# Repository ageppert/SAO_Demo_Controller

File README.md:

# SAO DEMO CONTROLLER

A Microcontroller for your smarter-than-average SAO!

The SAO Demo Controller makes it convenient to bring life to your advanced I2C-based SAO! Use this to test and demonstrate your new design even when your host badge isn't ready to control the SAO. Maybe this is better referred to as a micro badge for developing SAOs.

CAUTION: Do not plug this into your host badge and USB-C at the same time!!!

Follow this project at: https://hackaday.io/project/198034-sao-demo-controller 

Hardware Version 3.X
This one is protected for multiple power input options simultaneously with far more advanced power options, protection, and routing. This one is a perfect companion for an Etch sAo Sketch, Mac SAO, or any other SAO! See schematic for details and instructions.

Hardware Version 2.0 

Hardware Version 1.0

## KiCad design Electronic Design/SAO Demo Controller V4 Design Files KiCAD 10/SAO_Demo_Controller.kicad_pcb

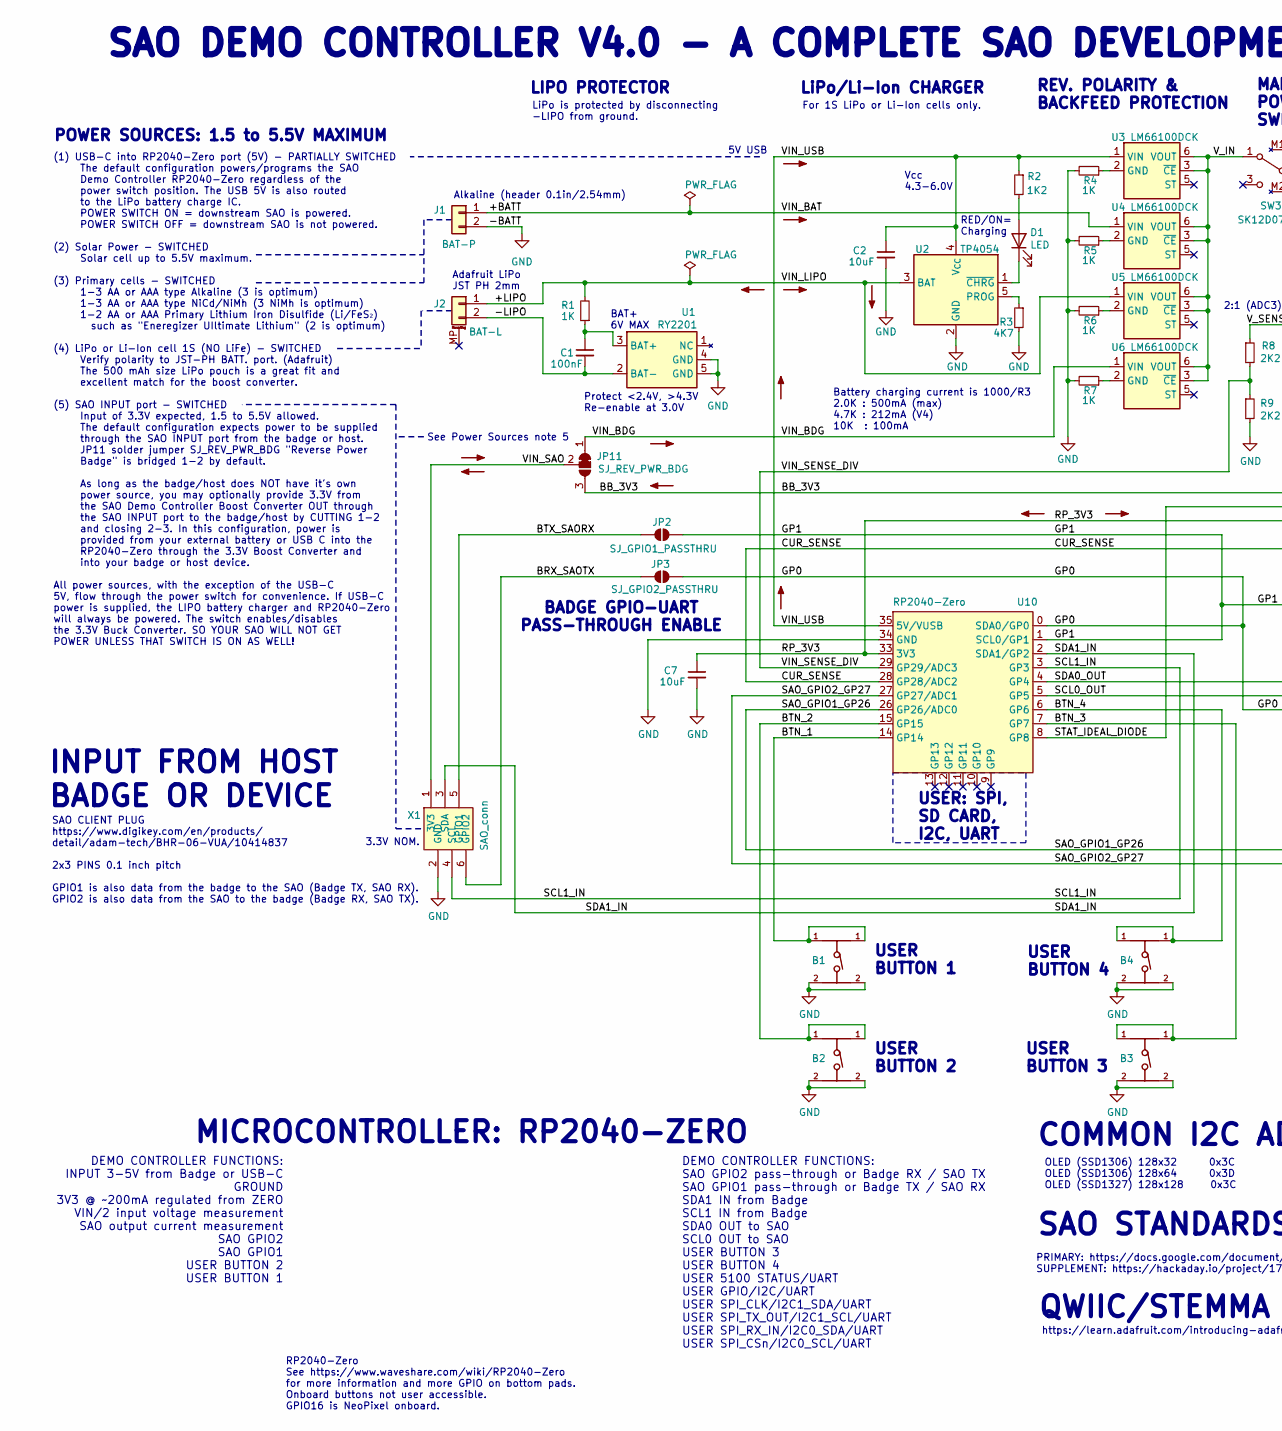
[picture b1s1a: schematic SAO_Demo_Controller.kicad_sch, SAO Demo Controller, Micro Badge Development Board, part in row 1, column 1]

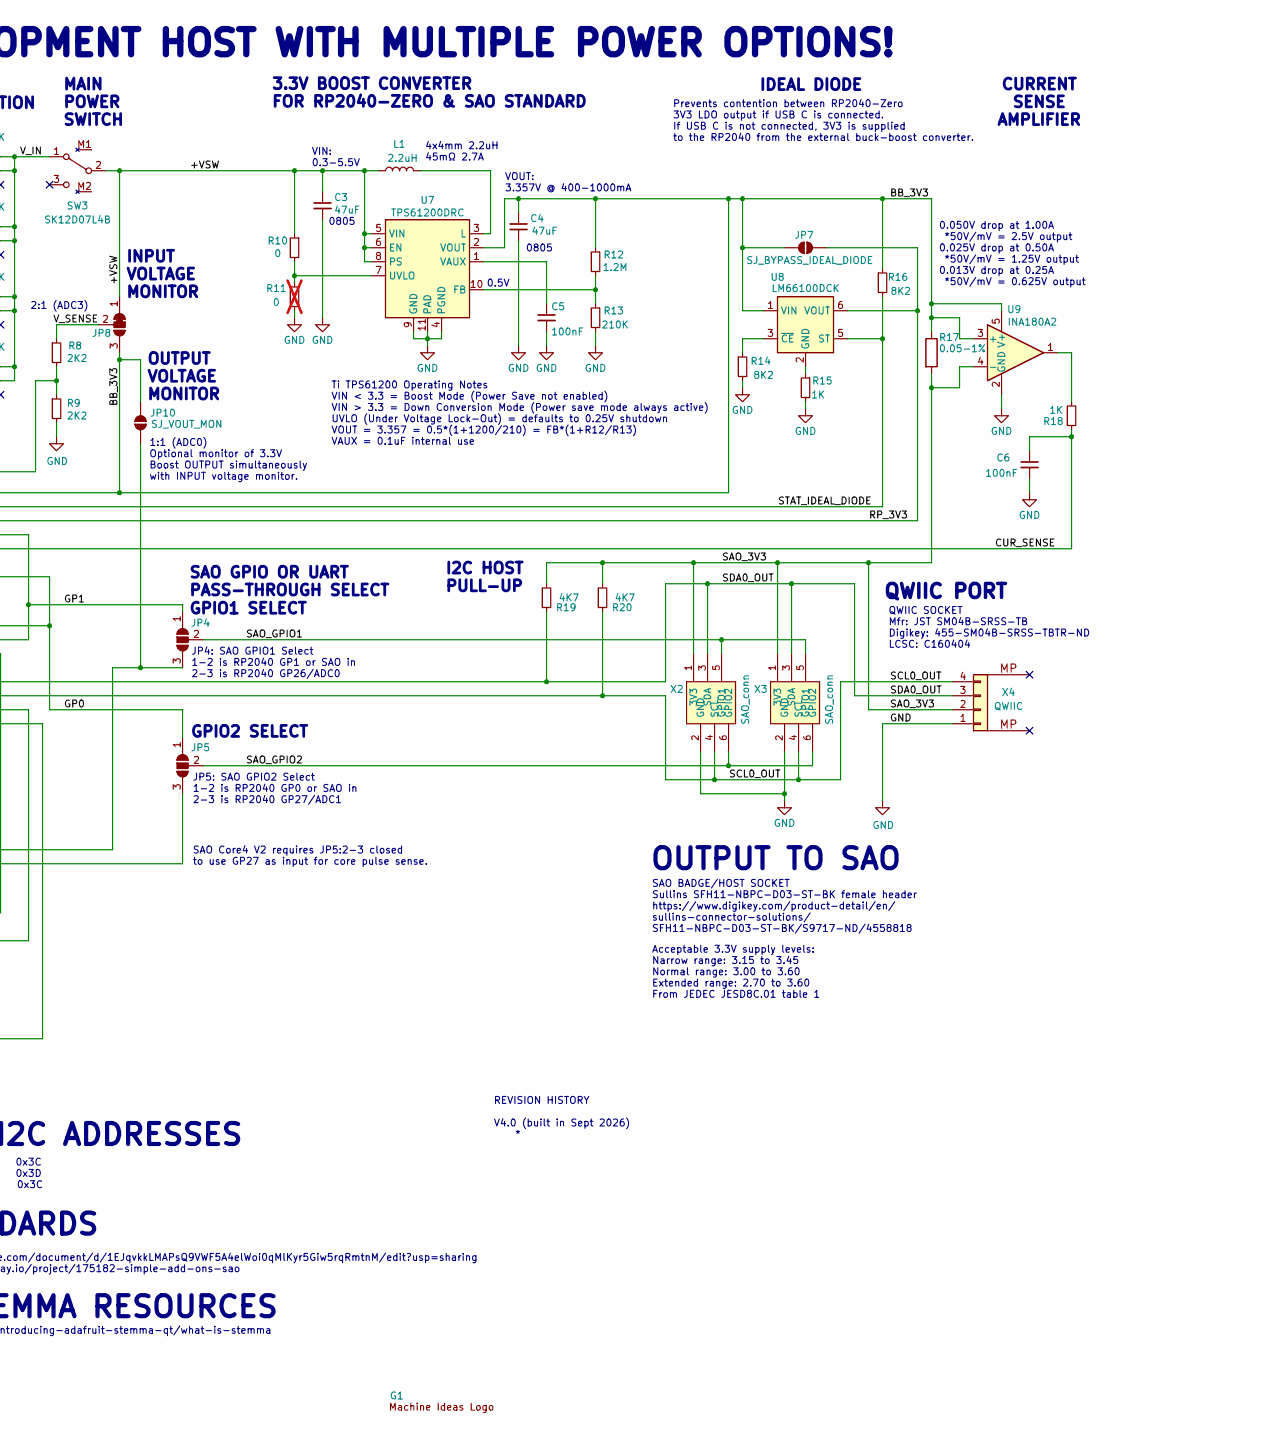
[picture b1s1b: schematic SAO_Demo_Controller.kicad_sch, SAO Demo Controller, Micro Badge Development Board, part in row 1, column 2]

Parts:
B1, B2, B3, B4: EVQP7J01P; SMD4_SW_EVQP7J_PAN; LCSC C2828254
C1, C5, C6: 100nF; C_0603_1608Metric; LCSC C14663
C2, C7: 10uF; C_0603_1608Metric; LCSC C19702
C3, C4: 47uF; C_0805_2012Metric; PART-NUMBER 10V 47uF X5R ±20% 0805; LCSC C16780
D1: LED; LED_0603_1608Metric; LCSC C2286
G1: Machine_Ideas_logo
J1: BAT-P; PinSocket_1x02_P2.54mm_Vertical
J2: BAT-L; JST_PH_S2B-PH-SM4-TB_1x02-1MP_P2.00mm_Horizontal; LCSC C295747
JP2: SJ_GPIO1_PASSTHRU; SolderJumper-2_P1.3mm_Open_RoundedPad1.0x1.5mm
JP3: SJ_GPIO2_PASSTHRU; SolderJumper-2_P1.3mm_Open_RoundedPad1.0x1.5mm
JP4, JP5: SolderJumper_3_Open; SolderJumper-3_P1.3mm_Open_RoundedPad1.0x1.5mm_NumberLabels
JP7: SJ_BYPASS_IDEAL_DIODE; SolderJumper-2_P1.3mm_Open_RoundedPad1.0x1.5mm
JP8: SolderJumper_3_Open; SolderJumper-3_P1.3mm_Bridged12_RoundedPad1.0x1.5mm
JP10: SJ_VOUT_MON; SolderJumper-2_P1.3mm_Open_RoundedPad1.0x1.5mm
JP11: SJ_REV_PWR_BDG; SolderJumper-3_P1.3mm_Bridged12_RoundedPad1.0x1.5mm
L1: 2.2uH; L_Sunlord_SWPA4020S; PART-NUMBER Sunltech Tech SLW4018S2R2MST; LCSC C206341
R1, R4, R5, R6, R7, R15, R18: 1K; R_0603_1608Metric; LCSC C21190
R2: 1K2; R_0603_1608Metric; LCSC C22765
R3, R19, R20: 4K7; R_0603_1608Metric; LCSC C23162
R8, R9: 2K2; R_0603_1608Metric; Manufacturer_Part_Number 0603WAF2201T5E; LCSC C4190
R10: 0; R_0603_1608Metric; LCSC C21189
R11: 0; R_0603_1608Metric; LCSC C21189; not fitted
R12: 1.2M; R_0603_1608Metric; LCSC C22766
R13: 210K; R_0603_1608Metric; LCSC C50670454
R14, R16: 8K2; R_0603_1608Metric; LCSC C25981
R17: 0.05-1%; R_0805_2012Metric; LCSC C5141277
SW3: SK12D07L4B; Switch_SK12D07VG4; LCSC C480340
U1: RY2201; SOT-23-5_HandSoldering; LCSC C370889
U2: TP4054; SOT-23-5; LCSC C32574
U3, U4, U5, U6, U8: LM66100DCK; SOT-363_SC-70-6; LCSC C2869734
U7: TPS61200DRC; Texas_S-PVSON-N10_ThermalVias; LCSC C140320
U9: INA180A2; SOT-23-5; LCSC C48533471
U10: RP2040-Zero; RP2040 Zero
X1: SAO_conn; Badgelife-SAOv169-BADGE-2x3-no-front-text; MPN SFH11-NBPC-D03-ST-BK
X2, X3: SAO_conn; Badgelife-SAOv169-BADGE-2x3-no-front-text-yes-front-outline; MPN SFH11-NBPC-D03-ST-BK
X4: QWIIC; JST_SH_SM04B-SRSS-TB_1x04-1MP_P1.00mm_Horizontal; MPN SM04B-SRSS-TB; LCSC C160404

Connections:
/+BATT: J1.1, U4.1 (VIN)
/+LIPO: J2.1, R1.2, U2.3 (BAT), U5.1 (VIN)
/+VSW: C3.1, JP8.1 (A), L1.2, R10.1, SW3.2 (B), U7.5 (VIN), U7.6 (EN), U7.8 (PS)
/-LIPO: C1.2, J2.2, U1.2 (BAT-)
/BB_3V3: C4.1, JP7.1 (A), JP8.3 (B), JP10.2 (B), JP11.3 (B), R12.1, R16.1, R17.1, U7.2 (VOUT), U8.1 (VIN), U9.3 (+), U9.5 (V+)
/BRX_SAOTX: JP3.1 (A), X1.6 (GPIO2)
/BTN_1: B1.1, U10.14 (GP14)
/BTN_2: B2.1, U10.15 (GP15)
/BTN_3: B3.1, U10.7 (GP7)
/BTN_4: B4.1, U10.6 (GP6)
/BTX_SAORX: JP2.1 (A), X1.5 (GPIO1)
/CUR_SENSE: C6.1, R18.1, U10.28 (GP28/ADC2)
/GP0: JP3.2 (B), JP5.1 (A), U10.0 (SDA0/GP0)
/GP1: JP2.2 (B), JP4.1 (A), U10.1 (SCL0/GP1)
/RP_3V3: C7.1, JP7.2 (B), U8.6 (VOUT), U10.33 (3V3)
/SAO_3V3: R17.2, R19.2, R20.2, U9.4 (-), X2.1 (3V3), X3.1 (3V3), X4.2
/SAO_GPIO1: JP4.2 (C), X2.5 (GPIO1), X3.5 (GPIO1)
/SAO_GPIO1_GP26: JP4.3 (B), JP10.1 (A), U10.26 (GP26/ADC0)
/SAO_GPIO2: JP5.2 (C), X2.6 (GPIO2), X3.6 (GPIO2)
/SAO_GPIO2_GP27: JP5.3 (B), U10.27 (GP27/ADC1)
/SCL0_OUT: R20.1, U10.5 (GP5), X2.4 (SCL), X3.4 (SCL), X4.4
/SCL1_IN: U10.3 (GP3), X1.4 (SCL)
/SDA0_OUT: R19.1, U10.4 (GP4), X2.3 (SDA), X3.3 (SDA), X4.3
/SDA1_IN: U10.2 (SDA1/GP2), X1.3 (SDA)
/STAT_IDEAL_DIODE: R16.2, U8.5 (ST), U10.8 (GP8)
/VIN_BDG: JP11.1 (A), U6.1 (VIN)
/VIN_SAO: JP11.2 (C), X1.1 (3V3)
/VIN_SENSE_DIV: R8.2, R9.1, U10.29 (GP29/ADC3)
/VIN_USB: C2.1, R2.1, U2.4 (V_{CC}), U3.1 (VIN), U10.35 (5V/VUSB)
/V_IN: SW3.1 (A), U3.3 (~CE), U3.6 (VOUT), U4.3 (~CE), U4.6 (VOUT), U5.3 (~CE), U5.6 (VOUT), U6.3 (~CE), U6.6 (VOUT)
/V_SENSE: JP8.2 (C), R8.1
GND: B1.2, B2.2, B3.2, B4.2, C2.2, C3.2, C4.2, C5.2, C6.2, C7.2, J1.2, R3.2, R4.2, R5.2, R6.2, R7.2, R9.2, R11.2, R13.2, R14.2, R15.2, U1.4 (GND), U1.5 (GND), U2.2 (GND), U7.4 (PGND), U7.9 (GND), U7.11 (PAD), U9.2 (GND), U10.34 (GND), X1.2 (GND), X2.2 (GND), X3.2 (GND), X4.1
unnamed: D1.2 (A), R2.2
unnamed: D1.1 (K), U2.1 (~CHRG)
unnamed: R18.2, U9.1
unnamed: C1.1, R1.1, U1.3 (BAT+)
unnamed: R3.1, U2.5 (PROG)
unnamed: R4.1, U3.2 (GND)
unnamed: R5.1, U4.2 (GND)
unnamed: R6.1, U5.2 (GND)
unnamed: R7.1, U6.2 (GND)
unnamed: R12.2, R13.1, U7.10 (FB)
unnamed: L1.1, U7.3 (L)
unnamed: R10.2, R11.1, U7.7 (UVLO)
unnamed: C5.1, U7.1 (VAUX)
unnamed: R15.1, U8.2 (GND)
unnamed: R14.1, U8.3 (~CE)

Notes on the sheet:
5V USB
REV. POLARITY & BACKFEED PROTECTION
SAO GPIO OR UART PASS-THROUGH SELECT
DEMO CONTROLLER FUNCTIONS: INPUT 3-5V from Badge or USB-C GROUND 3V3 @ ~200mA regulated from ZERO VIN/2 input voltage measurement SAO output current measurement SAO GPIO2 SAO GPIO1 USER BUTTON 2 USER BUTTON 1
Battery charging current is 1000/R3 2.0K : 500mA (max) 4.7K : 212mA (V4) 10K : 100mA
VOUT: 3.357V @ 400-1000mA
SAO BADGE/HOST SOCKET Sullins SFH11-NBPC-D03-ST-BK female header https://www.digikey.com/product-detail/en/ sullins-connector-solutions/ SFH11-NBPC-D03-ST-BK/S9717-ND/4558818
For 1S LiPo or Li-Ion cells only.
USER BUTTON 2
COMMON I2C ADDRESSES
QWIIC SOCKET Mfr: JST SM04B-SRSS-TB Digikey: 455-SM04B-SRSS-TBTR-ND LCSC: C160404
MAIN POWER SWITCH
USER BUTTON 1
Ti TPS61200 Operating Notes VIN < 3.3 = Boost Mode (Power Save not enabled) VIN > 3.3 = Down Conversion Mode (Power save mode always active) UVLO (Under Voltage Lock-Out) = defaults to 0.25V shutdown VOUT = 3.357 = 0.5*(1+1200/210) = FB*(1+R12/R13) VAUX = 0.1uF internal use
RP2040-Zero See https://www.waveshare.com/wiki/RP2040-Zero for more information and more GPIO on bottom pads. Onboard buttons not user accessible. GPIO16 is NeoPixel onboard.
USER: SPI, SD CARD, I2C, UART
GPIO1 SELECT
https://learn.adafruit.com/introducing-adafruit-stemma-qt/what-is-stemma
Acceptable 3.3V supply levels: Narrow range: 3.15 to 3.45 Normal range: 3.00 to 3.60 Extended range: 2.70 to 3.60 From JEDEC JESD8C.01 table 1
USER BUTTON 4
DEMO CONTROLLER FUNCTIONS: SAO GPIO2 pass-through or Badge RX / SAO TX SAO GPIO1 pass-through or Badge TX / SAO RX SDA1 IN from Badge SCL1 IN from Badge SDA0 OUT to SAO SCL0 OUT to SAO USER BUTTON 3 USER BUTTON 4 USER 5100 STATUS/UART USER GPIO/I2C/UART USER SPI_CLK/I2C1_SDA/UART USER SPI_TX_OUT/I2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
0805
0.050V drop at 1.00A *50V/mV = 2.5V output 0.025V drop at 0.50A *50V/mV = 1.25V output 0.013V drop at 0.25A *50V/mV = 0.625V output
SAO CLIENT PLUG https://www.digikey.com/en/products/ detail/adam-tech/BHR-06-VUA/10414837 2x3 PINS 0.1 inch pitch GPIO1 is also data from the badge to the SAO (Badge TX, SAO RX). GPIO2 is also data from the SAO to the badge (Badge RX, SAO TX).
3.3V NOM.
OLED (SSD1306) 128x32 0x3C OLED (SSD1306) 128x64 0x3D OLED (SSD1327) 128x128 0x3C
INPUT FROM HOST BADGE OR DEVICE
4x4mm 2.2uH 45mΩ 2.7A
Alkaline (header 0.1in/2.54mm)
BAT+ 6V MAX
QWIIC/STEMMA RESOURCES
IDEAL DIODE
RED/ON= Charging
SAO STANDARDS
Adafruit LiPo JST PH 2mm
I2C HOST PULL-UP
LIPO PROTECTOR
REVISION HISTORY V4.0 (built in Sept 2026) *
PRIMARY: https://docs.google.com/document/d/1EJqvkkLMAPsQ9VWF5A4elWoi0qMlKyr5Giw5rqRmtnM/edit?usp=sharing SUPPLEMENT: https://hackaday.io/project/175182-simple-add-ons-sao
INPUT VOLTAGE MONITOR

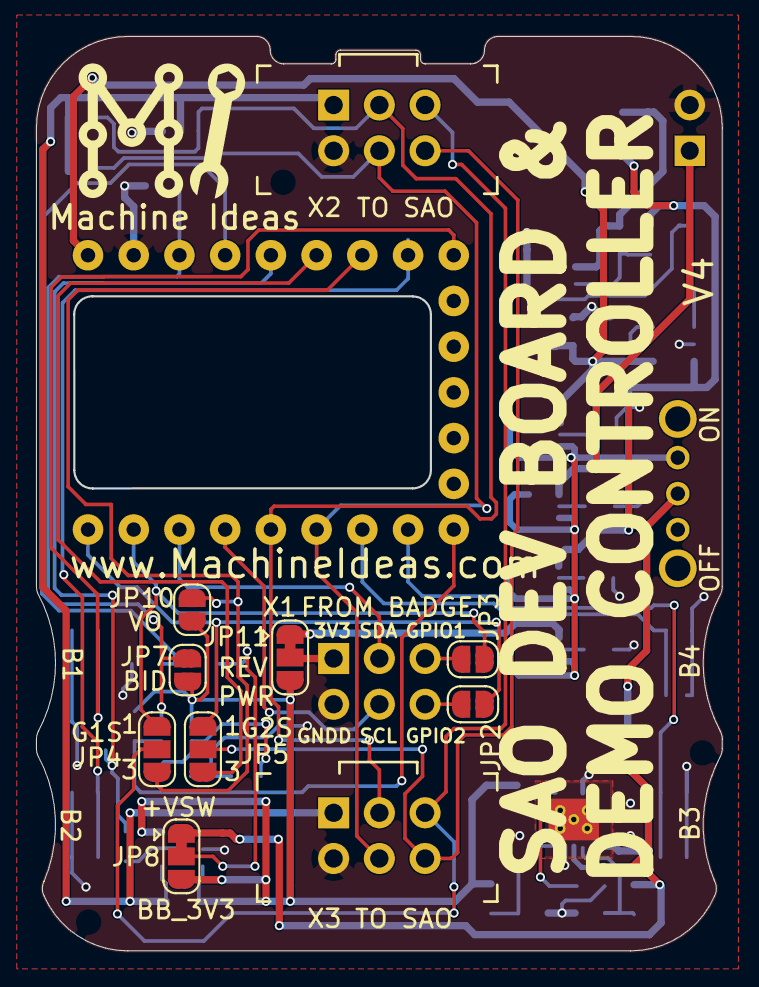
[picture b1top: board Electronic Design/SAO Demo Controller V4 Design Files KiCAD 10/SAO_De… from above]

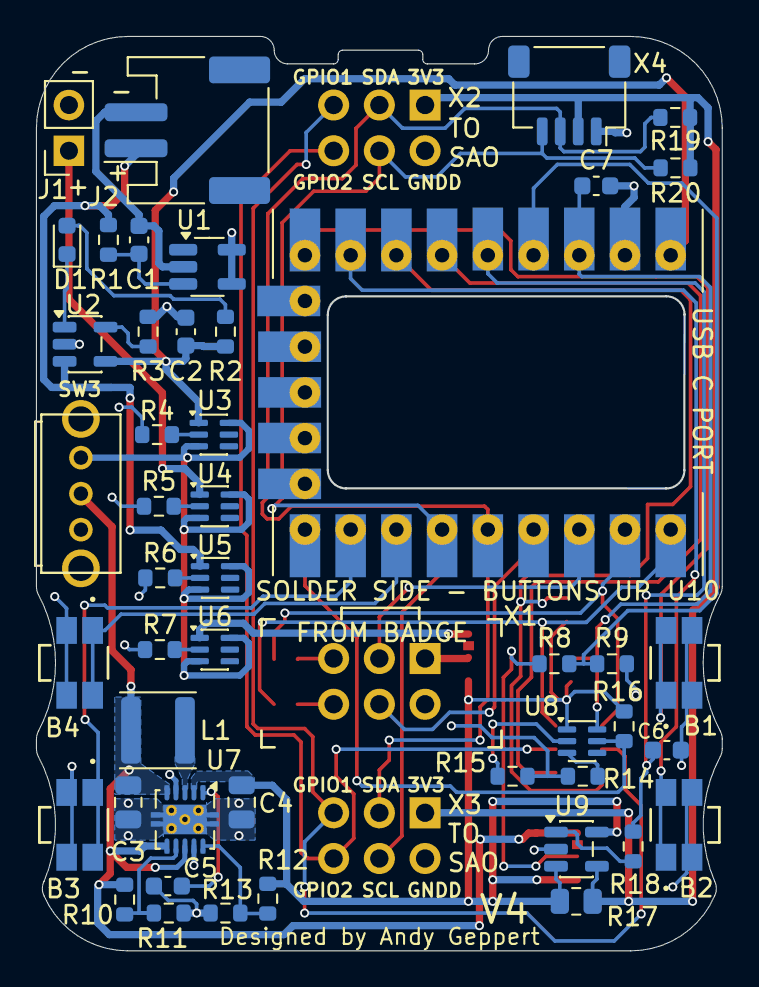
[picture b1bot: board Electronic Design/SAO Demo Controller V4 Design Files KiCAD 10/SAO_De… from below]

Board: 2 copper layers, 38.0 x 50.7 mm, 59 parts (47 on the bottom side), 47 nets.

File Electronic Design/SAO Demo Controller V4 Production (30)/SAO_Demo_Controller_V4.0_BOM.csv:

Designator,Footprint,Quantity,Value,LCSC Part #
"B1, B2, B3, B4",SMD4_SW_EVQP7J_PAN,4,EVQP7J01P,C2828254
"C1, C5, C6",0603,3,100nF,C14663
"C2, C7",0603,2,10uF,C19702
"C3, C4",0805,2,47uF,C16780
D1,0603,1,LED,C2286
J2,JST_PH_S2B-PH-SM4-TB_1x02-1MP_P2.00mm_Horizontal,1,BAT-L,C295747
L1,L_Sunlord_SWPA4020S,1,2.2uH,C206341
"R1, R15, R18, R4, R5, R6, R7",0603,7,1K,C21190
R10,0603,1,0,C21189
R12,0603,1,1.2M,C22766
R13,0603,1,210K,C50670454
"R14, R16",0603,2,8K2,C25981
R17,0805,1,0.05-1%,C5141277
"R19, R20, R3",0603,3,4K7,C23162
R2,0603,1,1K2,C22765
"R8, R9",0603,2,2K2,C4190
SW3,Switch_SK12D07VG4,1,SK12D07L4B,C480340
U1,SOT-23-5_HandSoldering,1,RY2201,C370889
U2,SOT-23-5,1,TP4054,C32574
"U3, U4, U5, U6, U8",SOT-363_SC-70-6,5,LM66100DCK,C2869734
U7,Texas_S-PVSON-N10_ThermalVias,1,TPS61200DRC,C140320
U9,SOT-23-5,1,INA180A2,C48533471
X4,JST_SH_SM04B-SRSS-TB_1x04-1MP_P1.00mm_Horizontal,1,QWIIC,C160404

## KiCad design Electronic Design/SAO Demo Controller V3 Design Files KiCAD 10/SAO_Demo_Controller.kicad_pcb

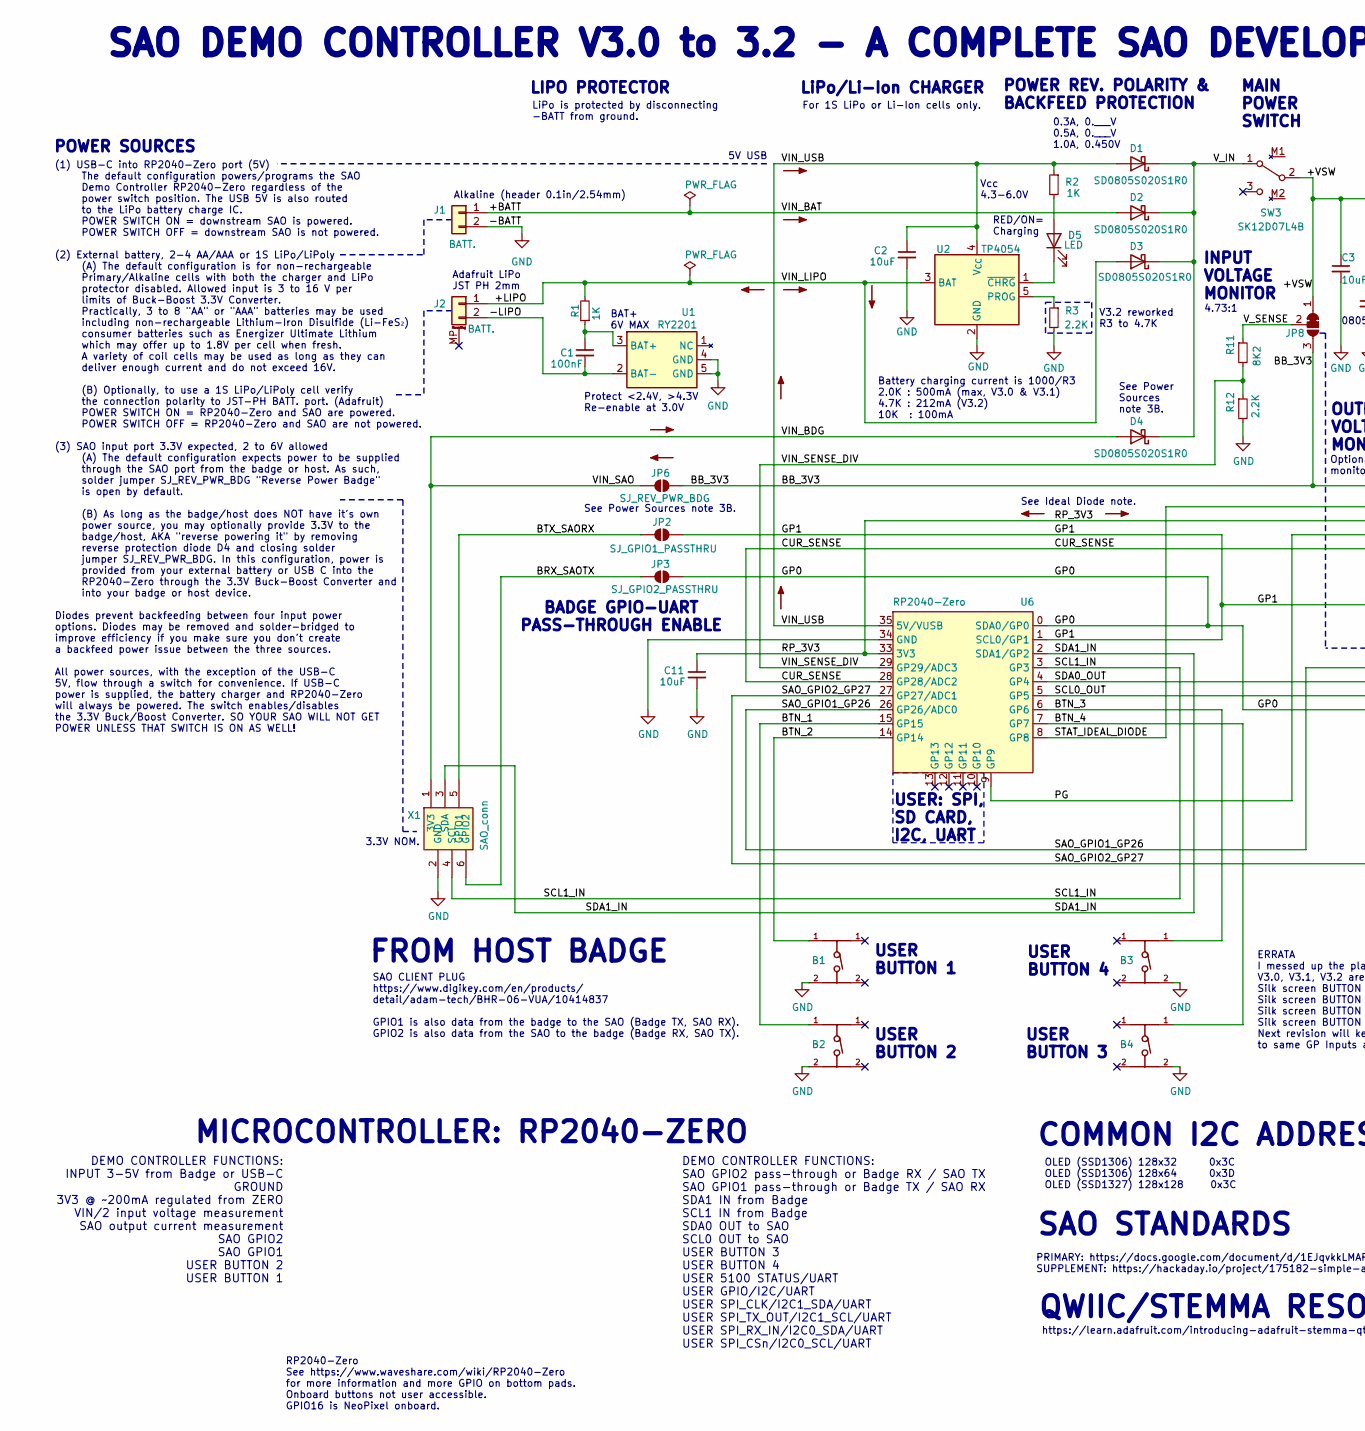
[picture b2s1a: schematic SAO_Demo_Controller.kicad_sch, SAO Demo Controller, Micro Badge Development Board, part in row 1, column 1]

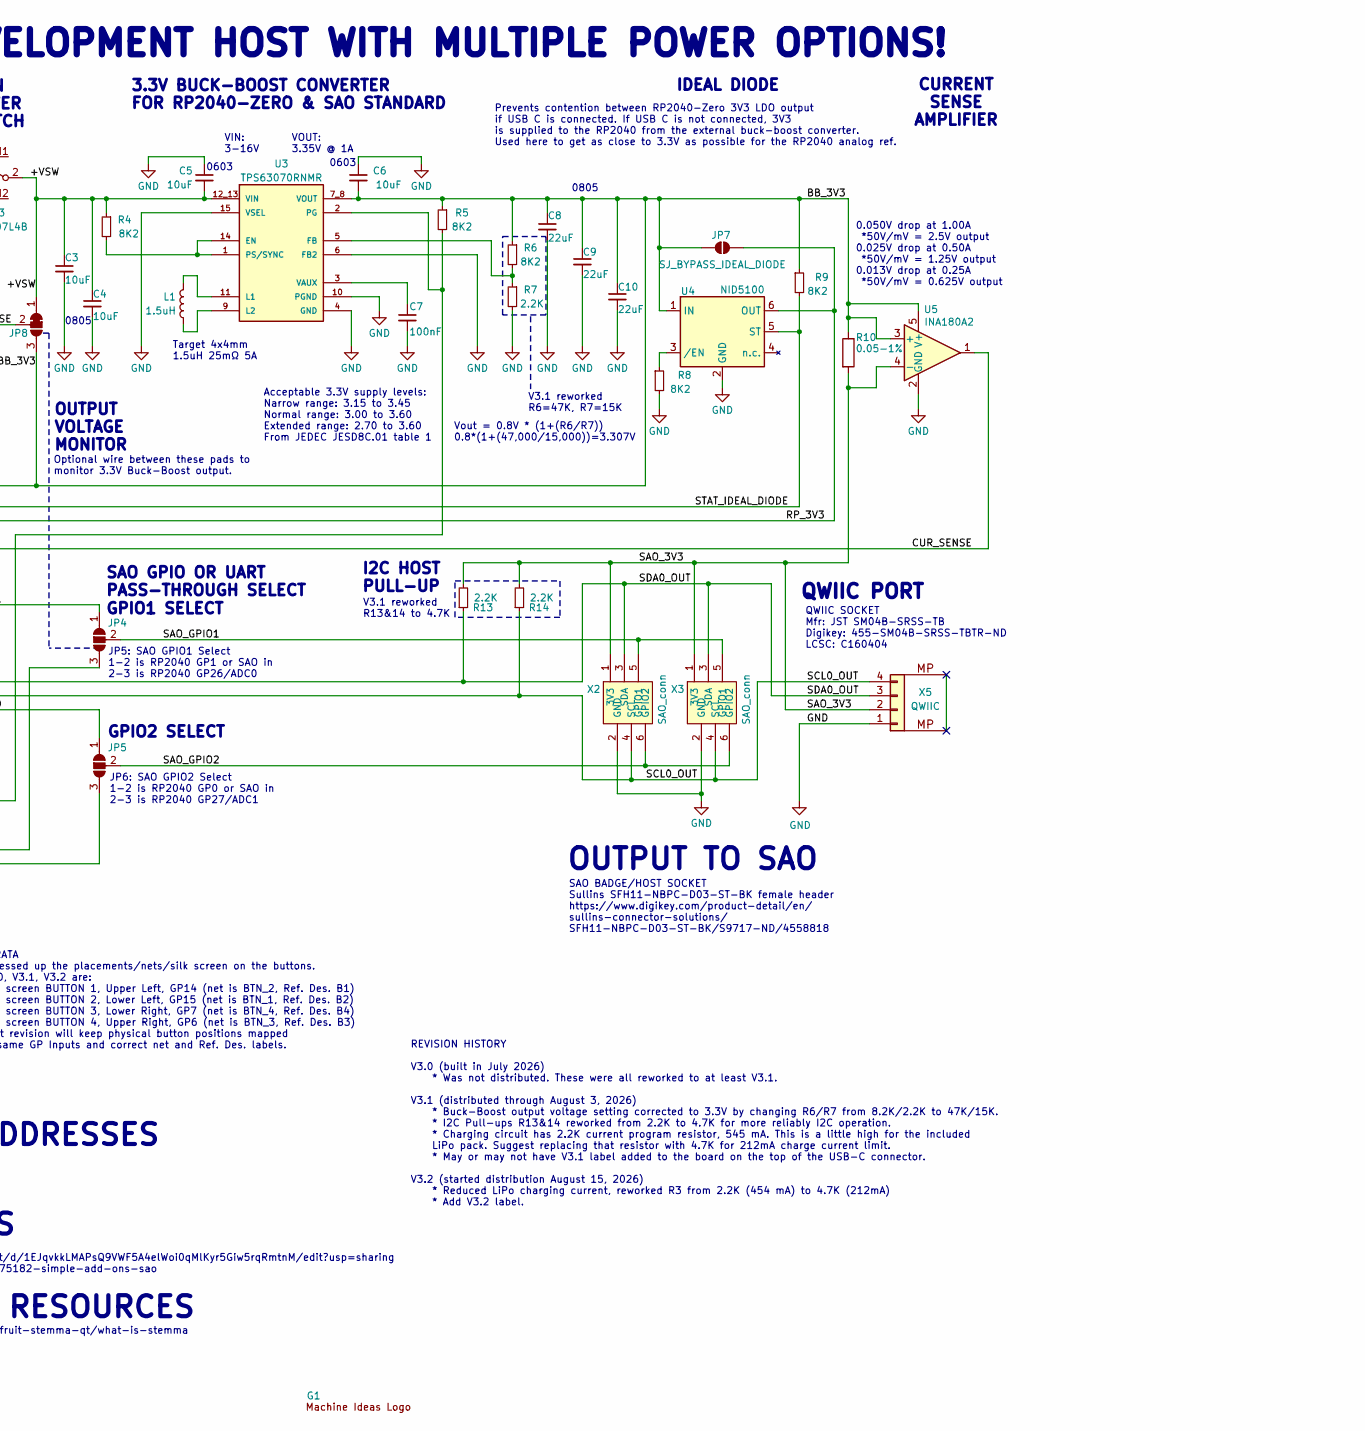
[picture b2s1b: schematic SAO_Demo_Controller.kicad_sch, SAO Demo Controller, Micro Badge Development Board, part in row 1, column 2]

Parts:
B1, B2, B3, B4: EVQP7J01P; SMD4_SW_EVQP7J_PAN; LCSC C2828254
C1, C7: 100nF; C_0603_1608Metric; LCSC C14663
C2, C6: 10uF; C_0603_1608Metric; LCSC C19702
C3, C4, C11: 10uF; C_0805_2012Metric; LCSC C15850
C5: 10uF; C_0603_1608Metric; LCSC C96446
C8, C9, C10: 22uF; C_0805_2012Metric; LCSC C45783
D1, D2, D3, D4: SD0805S020S1R0; D_0805_2012Metric; LCSC C143773
D5: LED; LED_0603_1608Metric; LCSC C2286
G1: Machine_Ideas_logo
J1: BATT.; PinSocket_1x02_P2.54mm_Vertical
J2: BATT.; JST_PH_S2B-PH-SM4-TB_1x02-1MP_P2.00mm_Horizontal; LCSC C295747
JP2: SJ_GPIO1_PASSTHRU; SolderJumper-2_P1.3mm_Open_RoundedPad1.0x1.5mm
JP3: SJ_GPIO2_PASSTHRU; SolderJumper-2_P1.3mm_Open_RoundedPad1.0x1.5mm
JP4, JP5: SolderJumper_3_Open; SolderJumper-3_P1.3mm_Open_RoundedPad1.0x1.5mm_NumberLabels
JP6: SJ_REV_PWR_BDG; SolderJumper-2_P1.3mm_Open_RoundedPad1.0x1.5mm
JP7: SJ_BYPASS_IDEAL_DIODE; SolderJumper-2_P1.3mm_Open_RoundedPad1.0x1.5mm
JP8: SolderJumper_3_Open; SolderJumper-3_P1.3mm_Bridged12_RoundedPad1.0x1.5mm
L1: 1.5uH; L_Sunlord_SWPA4020S; LCSC C98360
R1, R2: 1K; R_0603_1608Metric; LCSC C21190
R3, R7, R13, R14: 2.2K; R_0603_1608Metric; LCSC C4190
R4, R5, R6, R8, R9: 8K2; R_0603_1608Metric; LCSC C25981
R10: 0.05-1%; R_0805_2012Metric; LCSC C5141277
R11: 8K2; R_0603_1608Metric; Manufacturer_Part_Number RK73H2ATTD3301F; LCSC C25981
R12: 2.2K; R_0603_1608Metric; Manufacturer_Part_Number RK73H2ATTD3301F; LCSC C4190
SW3: SK12D07L4B; Switch_SK12D07VG4; LCSC C480340
U1: RY2201; SOT-23-5_HandSoldering; LCSC C370889
U2: TP4054; SOT-23-5; LCSC C382138
U3: TPS63070RNMR; VREG_TPS63070RNMR; PARTREV B; LCSC C109322
U4: NID5100; SOT-363_SC-70-6; LCSC C40065155
U5: INA180A2; SOT-23-5; LCSC C192764
U6: RP2040-Zero; RP2040 Zero
X1: SAO_conn; Badgelife-SAOv169-BADGE-2x3-no-front-text; MPN SFH11-NBPC-D03-ST-BK
X2, X3: SAO_conn; Badgelife-SAOv169-BADGE-2x3-no-front-text-yes-front-outline; MPN SFH11-NBPC-D03-ST-BK
X5: QWIIC; JST_SH_SM04B-SRSS-TB_1x04-1MP_P1.00mm_Horizontal; MPN SM04B-SRSS-TB; LCSC C160404

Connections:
/+BATT: D2.2 (A), J1.1
/+LIPO: D3.2 (A), J2.1, R1.2, U2.3 (BAT)
/+VSW: C3.1, C4.1, C5.2, JP8.1 (A), R4.1, SW3.2 (B), U3.12_13 (VIN)
/-LIPO: C1.2, J2.2, U1.2 (BAT-)
/BB_3V3: C6.2, C8.1, C9.1, C10.1, JP6.2 (B), JP7.1 (A), JP8.3 (B), R5.1, R6.1, R9.1, R10.1, U3.7_8 (VOUT), U4.1 (IN), U5.3 (+), U5.5 (V+)
/BRX_SAOTX: JP3.1 (A), X1.6 (GPIO2)
/BTN_1: B2.1, U6.15 (GP15)
/BTN_2: B1.1, U6.14 (GP14)
/BTN_3: B3.1, U6.6 (GP6)
/BTN_4: B4.1, U6.7 (GP7)
/BTX_SAORX: JP2.1 (A), X1.5 (GPIO1)
/CUR_SENSE: U5.1, U6.28 (GP28/ADC2)
/GP0: JP3.2 (B), JP5.1 (A), U6.0 (SDA0/GP0)
/GP1: JP2.2 (B), JP4.1 (A), U6.1 (SCL0/GP1)
/PG: R5.2, U3.2 (PG), U6.9 (GP9)
/RP_3V3: C11.1, JP7.2 (B), U4.6 (OUT), U6.33 (3V3)
/SAO_3V3: R10.2, R13.2, R14.2, U5.4 (-), X2.1 (3V3), X3.1 (3V3), X5.2
/SAO_GPIO1: JP4.2 (C), X2.5 (GPIO1), X3.5 (GPIO1)
/SAO_GPIO1_GP26: JP4.3 (B), U6.26 (GP26/ADC0)
/SAO_GPIO2: JP5.2 (C), X2.6 (GPIO2), X3.6 (GPIO2)
/SAO_GPIO2_GP27: JP5.3 (B), U6.27 (GP27/ADC1)
/SCL0_OUT: R14.1, U6.5 (GP5), X2.4 (SCL), X3.4 (SCL), X5.4
/SCL1_IN: U6.3 (GP3), X1.4 (SCL)
/SDA0_OUT: R13.1, U6.4 (GP4), X2.3 (SDA), X3.3 (SDA), X5.3
/SDA1_IN: U6.2 (SDA1/GP2), X1.3 (SDA)
/STAT_IDEAL_DIODE: R9.2, U4.5 (ST), U6.8 (GP8)
/VIN_BDG: D4.2 (A), JP6.1 (A), X1.1 (3V3)
/VIN_SENSE_DIV: R11.2, R12.1, U6.29 (GP29/ADC3)
/VIN_USB: C2.1, D1.2 (A), R2.1, U2.4 (V_{CC}), U6.35 (5V/VUSB)
/V_IN: D1.1 (K), D2.1 (K), D3.1 (K), D4.1 (K), SW3.1 (A)
/V_SENSE: JP8.2 (C), R11.1
GND: B1.2, B2.2, B3.2, B4.2, C2.2, C3.2, C4.2, C5.1, C6.1, C7.2, C8.2, C9.2, C10.2, C11.2, J1.2, R3.2, R7.2, R8.2, R12.2, U1.4 (GND), U1.5 (GND), U2.2 (GND), U3.4 (GND), U3.6 (FB2), U3.10 (PGND), U3.15 (VSEL), U4.2 (GND), U5.2 (GND), U6.34 (GND), X1.2 (GND), X2.2 (GND), X3.2 (GND), X5.1
unnamed: D5.2 (A), R2.2
unnamed: D5.1 (K), U2.1 (~CHRG)
unnamed: C1.1, R1.1, U1.3 (BAT+)
unnamed: R3.1, U2.5 (PROG)
unnamed: R4.2, U3.1 (PS/SYNC), U3.14 (EN)
unnamed: R6.2, R7.1, U3.5 (FB)
unnamed: L1.1, U3.11 (L1)
unnamed: L1.2, U3.9 (L2)
unnamed: C7.1, U3.3 (VAUX)
unnamed: R8.1, U4.3 (/EN)

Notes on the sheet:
5V USB
POWER REV. POLARITY & BACKFEED PROTECTION
SAO GPIO OR UART PASS-THROUGH SELECT
DEMO CONTROLLER FUNCTIONS: INPUT 3-5V from Badge or USB-C GROUND 3V3 @ ~200mA regulated from ZERO VIN/2 input voltage measurement SAO output current measurement SAO GPIO2 SAO GPIO1 USER BUTTON 2 USER BUTTON 1
Battery charging current is 1000/R3 2.0K : 500mA (max, V3.0 & V3.1) 4.7K : 212mA (V3.2) 10K : 100mA
See Ideal Diode note.
SAO BADGE/HOST SOCKET Sullins SFH11-NBPC-D03-ST-BK female header https://www.digikey.com/product-detail/en/ sullins-connector-solutions/ SFH11-NBPC-D03-ST-BK/S9717-ND/4558818
For 1S LiPo or Li-Ion cells only.
USER BUTTON 2
COMMON I2C ADDRESSES
QWIIC SOCKET Mfr: JST SM04B-SRSS-TB Digikey: 455-SM04B-SRSS-TBTR-ND LCSC: C160404
MAIN POWER SWITCH
USER BUTTON 1
0805
RP2040-Zero See https://www.waveshare.com/wiki/RP2040-Zero for more information and more GPIO on bottom pads. Onboard buttons not user accessible. GPIO16 is NeoPixel onboard.
USER: SPI, SD CARD, I2C, UART
V3.1 reworked R6=47K, R7=15K
GPIO1 SELECT
https://learn.adafruit.com/introducing-adafruit-stemma-qt/what-is-stemma
Acceptable 3.3V supply levels: Narrow range: 3.15 to 3.45 Normal range: 3.00 to 3.60 Extended range: 2.70 to 3.60 From JEDEC JESD8C.01 table 1
USER BUTTON 4
DEMO CONTROLLER FUNCTIONS: SAO GPIO2 pass-through or Badge RX / SAO TX SAO GPIO1 pass-through or Badge TX / SAO RX SDA1 IN from Badge SCL1 IN from Badge SDA0 OUT to SAO SCL0 OUT to SAO USER BUTTON 3 USER BUTTON 4 USER 5100 STATUS/UART USER GPIO/I2C/UART USER SPI_CLK/I2C1_SDA/UART USER SPI_TX_OUT/I2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
ERRATA I messed up the placements/nets/silk screen on the buttons. V3.0, V3.1, V3.2 are: Silk screen BUTTON 1, Upper Left, GP14 (net is BTN_2, Ref. Des. B1) Silk screen BUTTON 2, Lower Left, GP15 (net is BTN_1, Ref. Des. B2) Silk screen BUTTON 3, Lower Right, GP7 (net is BTN_4, Ref. Des. B4) Silk s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
0603
0.050V drop at 1.00A *50V/mV = 2.5V output 0.025V drop at 0.50A *50V/mV = 1.25V output 0.013V drop at 0.25A *50V/mV = 0.625V output
SAO CLIENT PLUG https://www.digikey.com/en/products/ detail/adam-tech/BHR-06-VUA/10414837 GPIO1 is also data from the badge to the SAO (Badge TX, SAO RX). GPIO2 is also data from the SAO to the badge (Badge RX, SAO TX).
3.3V NOM.
OLED (SSD1306) 128x32 0x3C OLED (SSD1306) 128x64 0x3D OLED (SSD1327) 128x128 0x3C
FROM HOST BADGE
V3.1 reworked R13&14 to 4.7K
Alkaline (header 0.1in/2.54mm)
BAT+ 6V MAX
QWIIC/STEMMA RESOURCES
IDEAL DIODE
RED/ON= Charging
SAO STANDARDS
See Power Sources note 3B.
Adafruit LiPo JST PH 2mm
I2C HOST PULL-UP
LIPO PROTECTOR

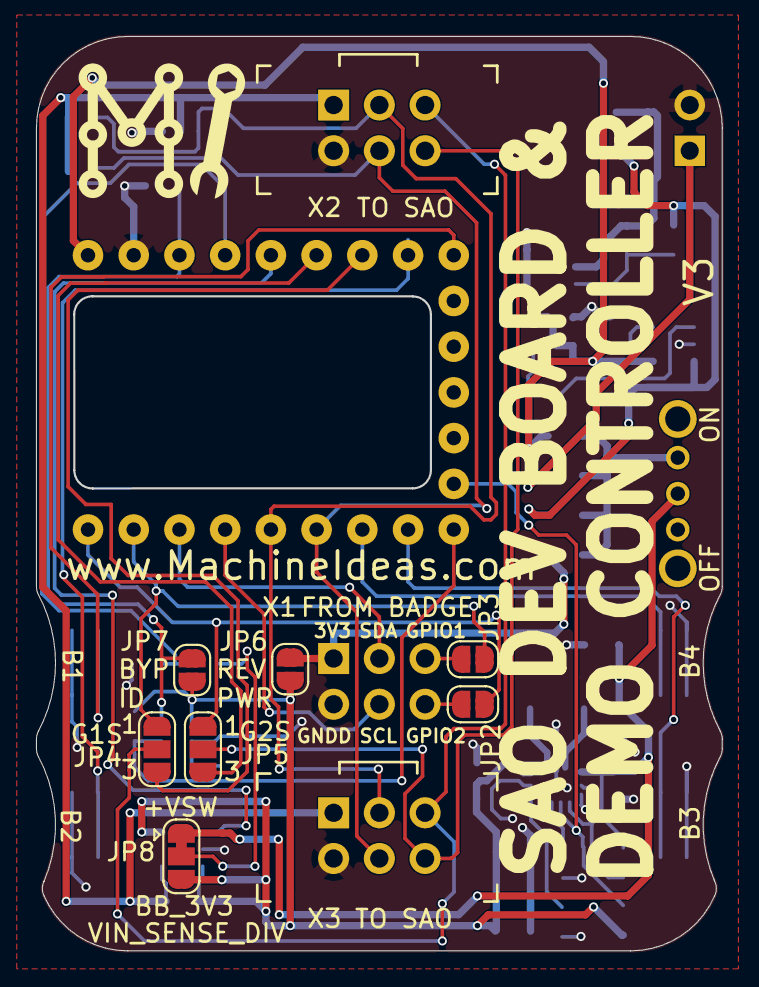
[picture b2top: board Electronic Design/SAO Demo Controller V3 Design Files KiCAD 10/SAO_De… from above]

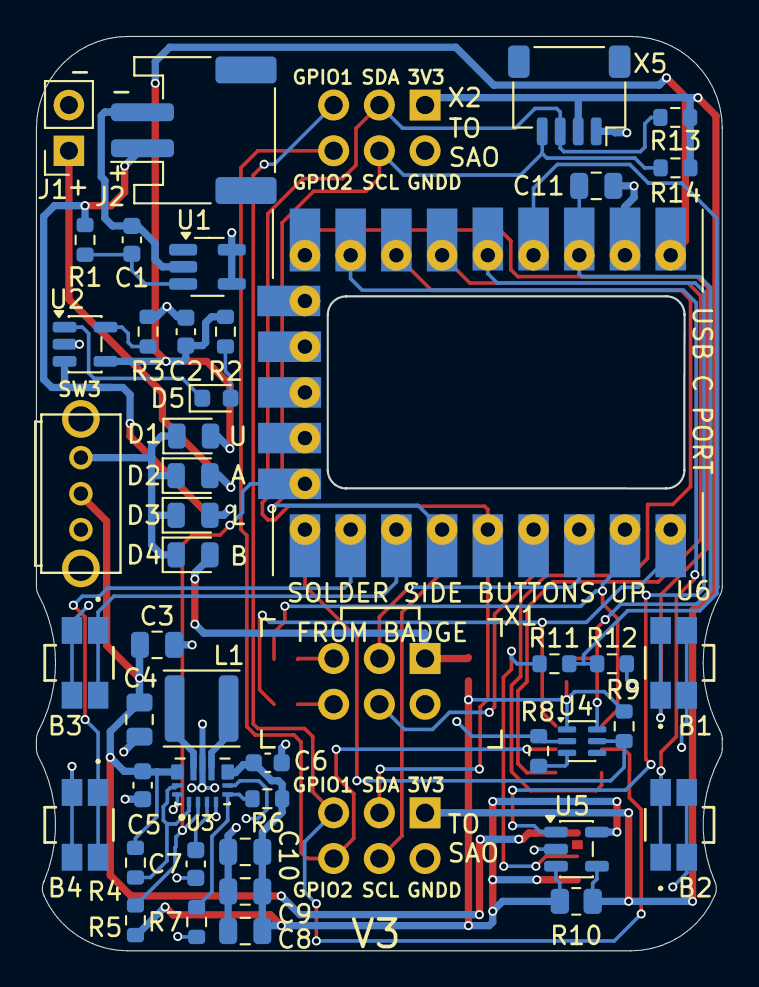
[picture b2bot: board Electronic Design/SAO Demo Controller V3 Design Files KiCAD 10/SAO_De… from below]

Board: 2 copper layers, 38.0 x 50.7 mm, 56 parts (45 on the bottom side), 42 nets.

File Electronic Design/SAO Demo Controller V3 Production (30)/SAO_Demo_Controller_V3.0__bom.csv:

Designator,Footprint,Quantity,Value,LCSC Part #
"B1, B2, B3, B4",SMD4_SW_EVQP7J_PAN,4,EVQP7J01P,C2828254
"C1, C7",0603,2,100nF,C14663
"C10, C8, C9",0805,3,22uF,C45783
"C11, C3, C4",0805,3,10uF,C15850
"C2, C6",0603,2,10uF,C19702
C5,0603,1,10uF,C96446
"D1, D2, D3, D4",0805,4,SD0805S020S1R0,C143773
D5,0603,1,LED,C2286
J2,JST_PH_S2B-PH-SM4-TB_1x02-1MP_P2.00mm_Horizontal,1,BATT.,C295747
L1,L_Sunlord_SWPA4020S,1,1.5uH,C98360
"R1, R2",0603,2,1K,C21190
R10,0805,1,0.05-1%,C5141277
"R11, R4, R5, R6, R8, R9",0603,6,8K2,C25981
"R12, R13, R14, R3, R7",0603,5,2.2K,C4190
SW3,Switch_SK12D07VG4,1,SK12D07L4B,C480340
U1,SOT-23-5_HandSoldering,1,RY2201,C370889
U2,SOT-23-5,1,TP4054,C382138
U3,VREG_TPS63070RNMR,1,TPS63070RNMR,C109322
U4,SOT-363_SC-70-6,1,NID5100,C40065155
U5,SOT-23-5,1,INA180A2,C192764
X5,JST_SH_SM04B-SRSS-TB_1x04-1MP_P1.00mm_Horizontal,1,QWIIC,C160404
